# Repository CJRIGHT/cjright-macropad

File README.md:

# cjright-macropad
A custom 3 key macropad made for convenience with: KiCad and AutoCad Fusion.

This is my first time every participating in a event such as Stardance, this first project has been very fun to work through and I have learnt so much. Thanks to the event organisers and partners for making it possible.

I decided to try it since once I finish school I really would like to get into software engineering or something similar I figured it's good to learn as much about electronics as possible to help my chances of succeeding. 

# 📷 Gallery

*Assembled product*

*Top Part*

*Bottom Part*

*Schematic Design*

*PCB Design*

# 📦 BoM 

| Item Name | Quantity | Purpose |
| --------- | -------- | ------- |
| XIAO RP2040 | 1 | Seeed Studio XIAO RP2040  |
| Custom PCB | 1 | Board made in KiCad | 
| MX-Style Switches | 3 | Keyboard Switches |
| Keycaps | 3 | Any available keycaps |
| Heatset Inserts | 4| M3×5×4mm heatset inserts |
| M3 Screws | 4 | M3 × 16 mm screws |
| Bottom Case | 1 | 3D Printed `KeyboardCaseBottom.step` |
| Top Case | 1 | 3D Printed `KeyboardCaseTop.step` |

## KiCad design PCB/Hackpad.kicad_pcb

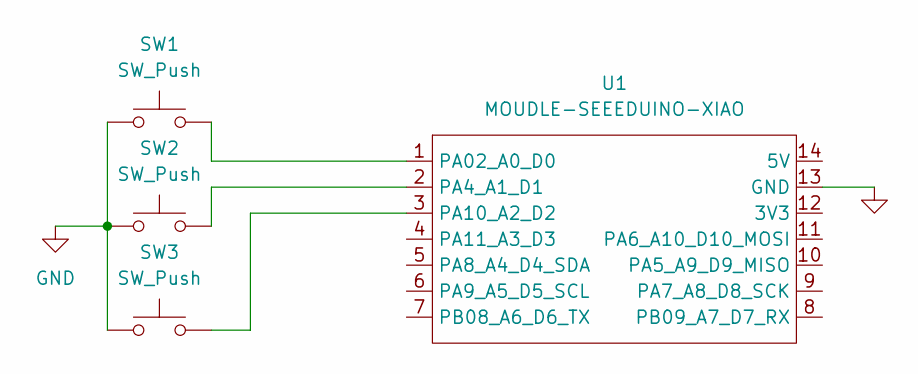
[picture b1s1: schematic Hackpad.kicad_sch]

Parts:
SW1, SW2, SW3: SW_Push; SW_Cherry_MX_1.00u_PCB
U1: MOUDLE-SEEEDUINO-XIAO; XIAO-Generic-Hybrid-14P-2.54-21X17.8MM

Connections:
GND: SW1.1, SW2.1, SW3.1, U1.13 (GND)
unnamed: SW1.2, U1.1 (PA02_A0_D0)
unnamed: SW2.2, U1.2 (PA4_A1_D1)
unnamed: SW3.2, U1.3 (PA10_A2_D2)

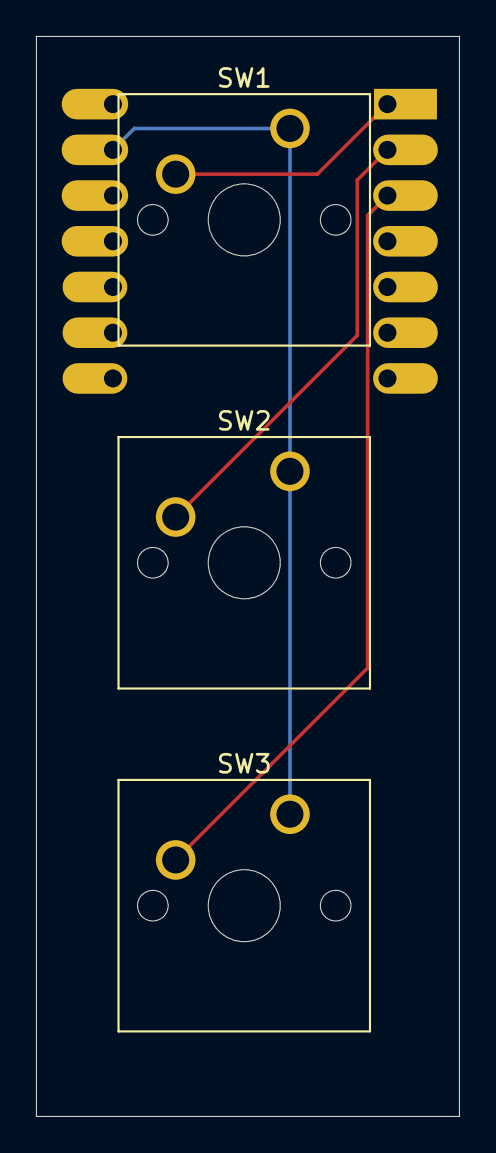
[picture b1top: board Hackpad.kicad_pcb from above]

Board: 2 copper layers, 23.5 x 60.0 mm, 4 parts (1 on the bottom side), 4 nets.

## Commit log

2026-06-06 Update README with project details and images
    Added a personal reflection on participating in Stardance and included a gallery of images showcasing the project.
2026-06-06 Create CAD
